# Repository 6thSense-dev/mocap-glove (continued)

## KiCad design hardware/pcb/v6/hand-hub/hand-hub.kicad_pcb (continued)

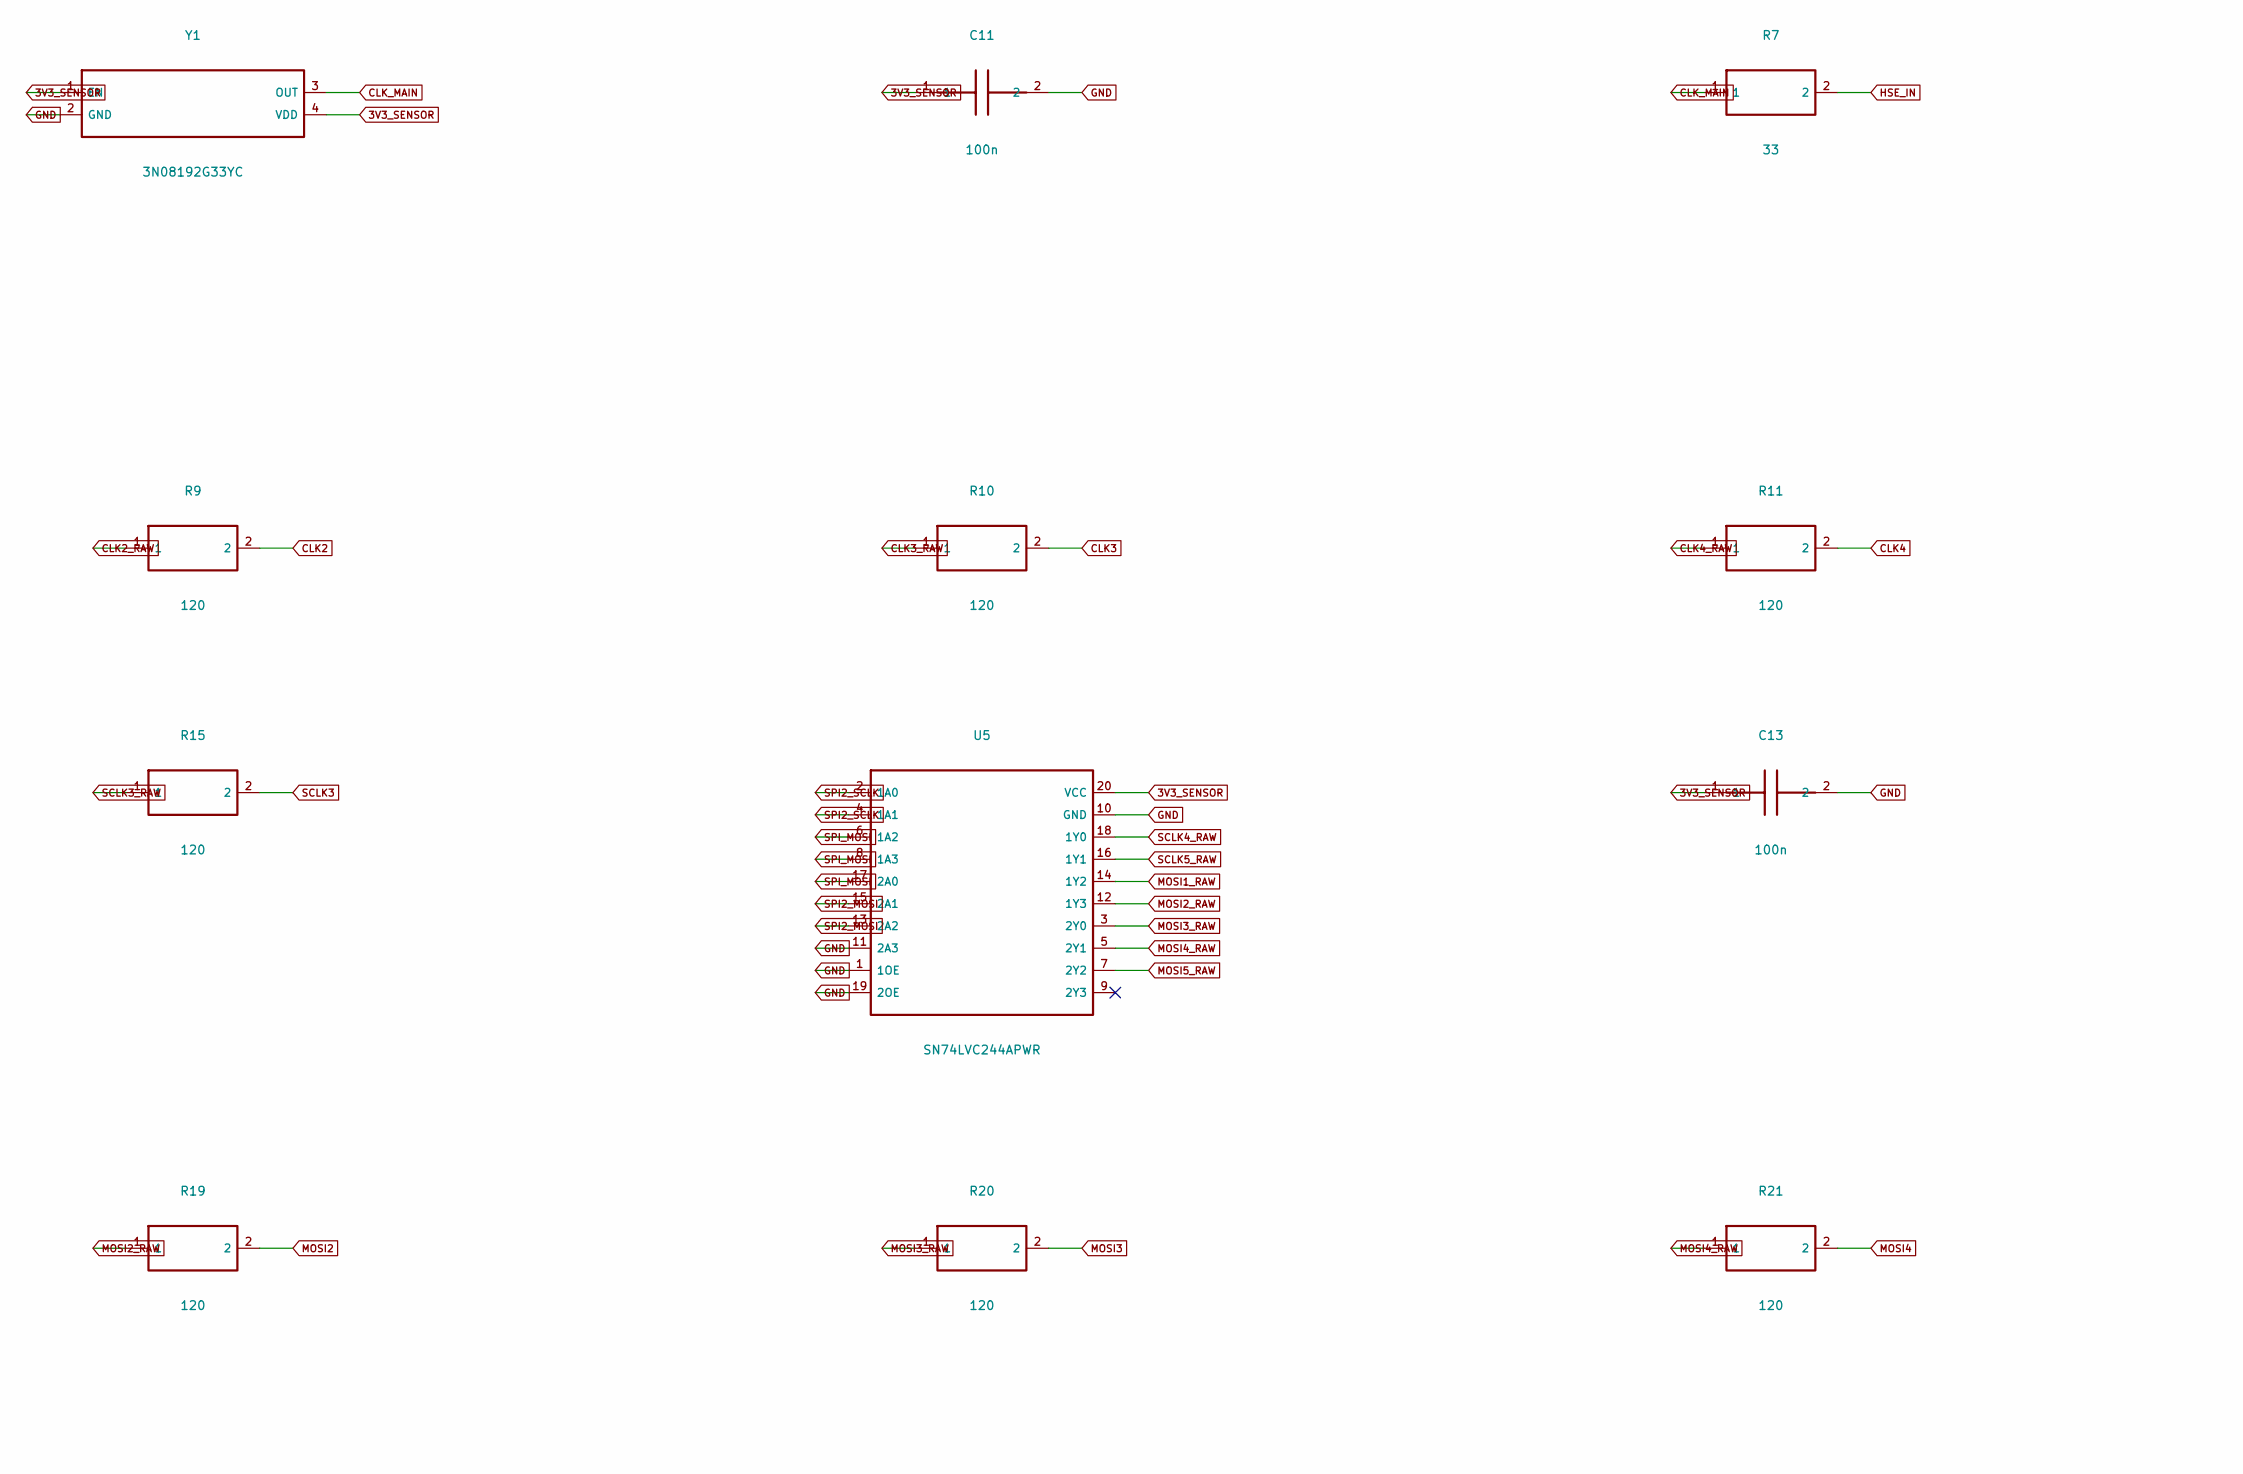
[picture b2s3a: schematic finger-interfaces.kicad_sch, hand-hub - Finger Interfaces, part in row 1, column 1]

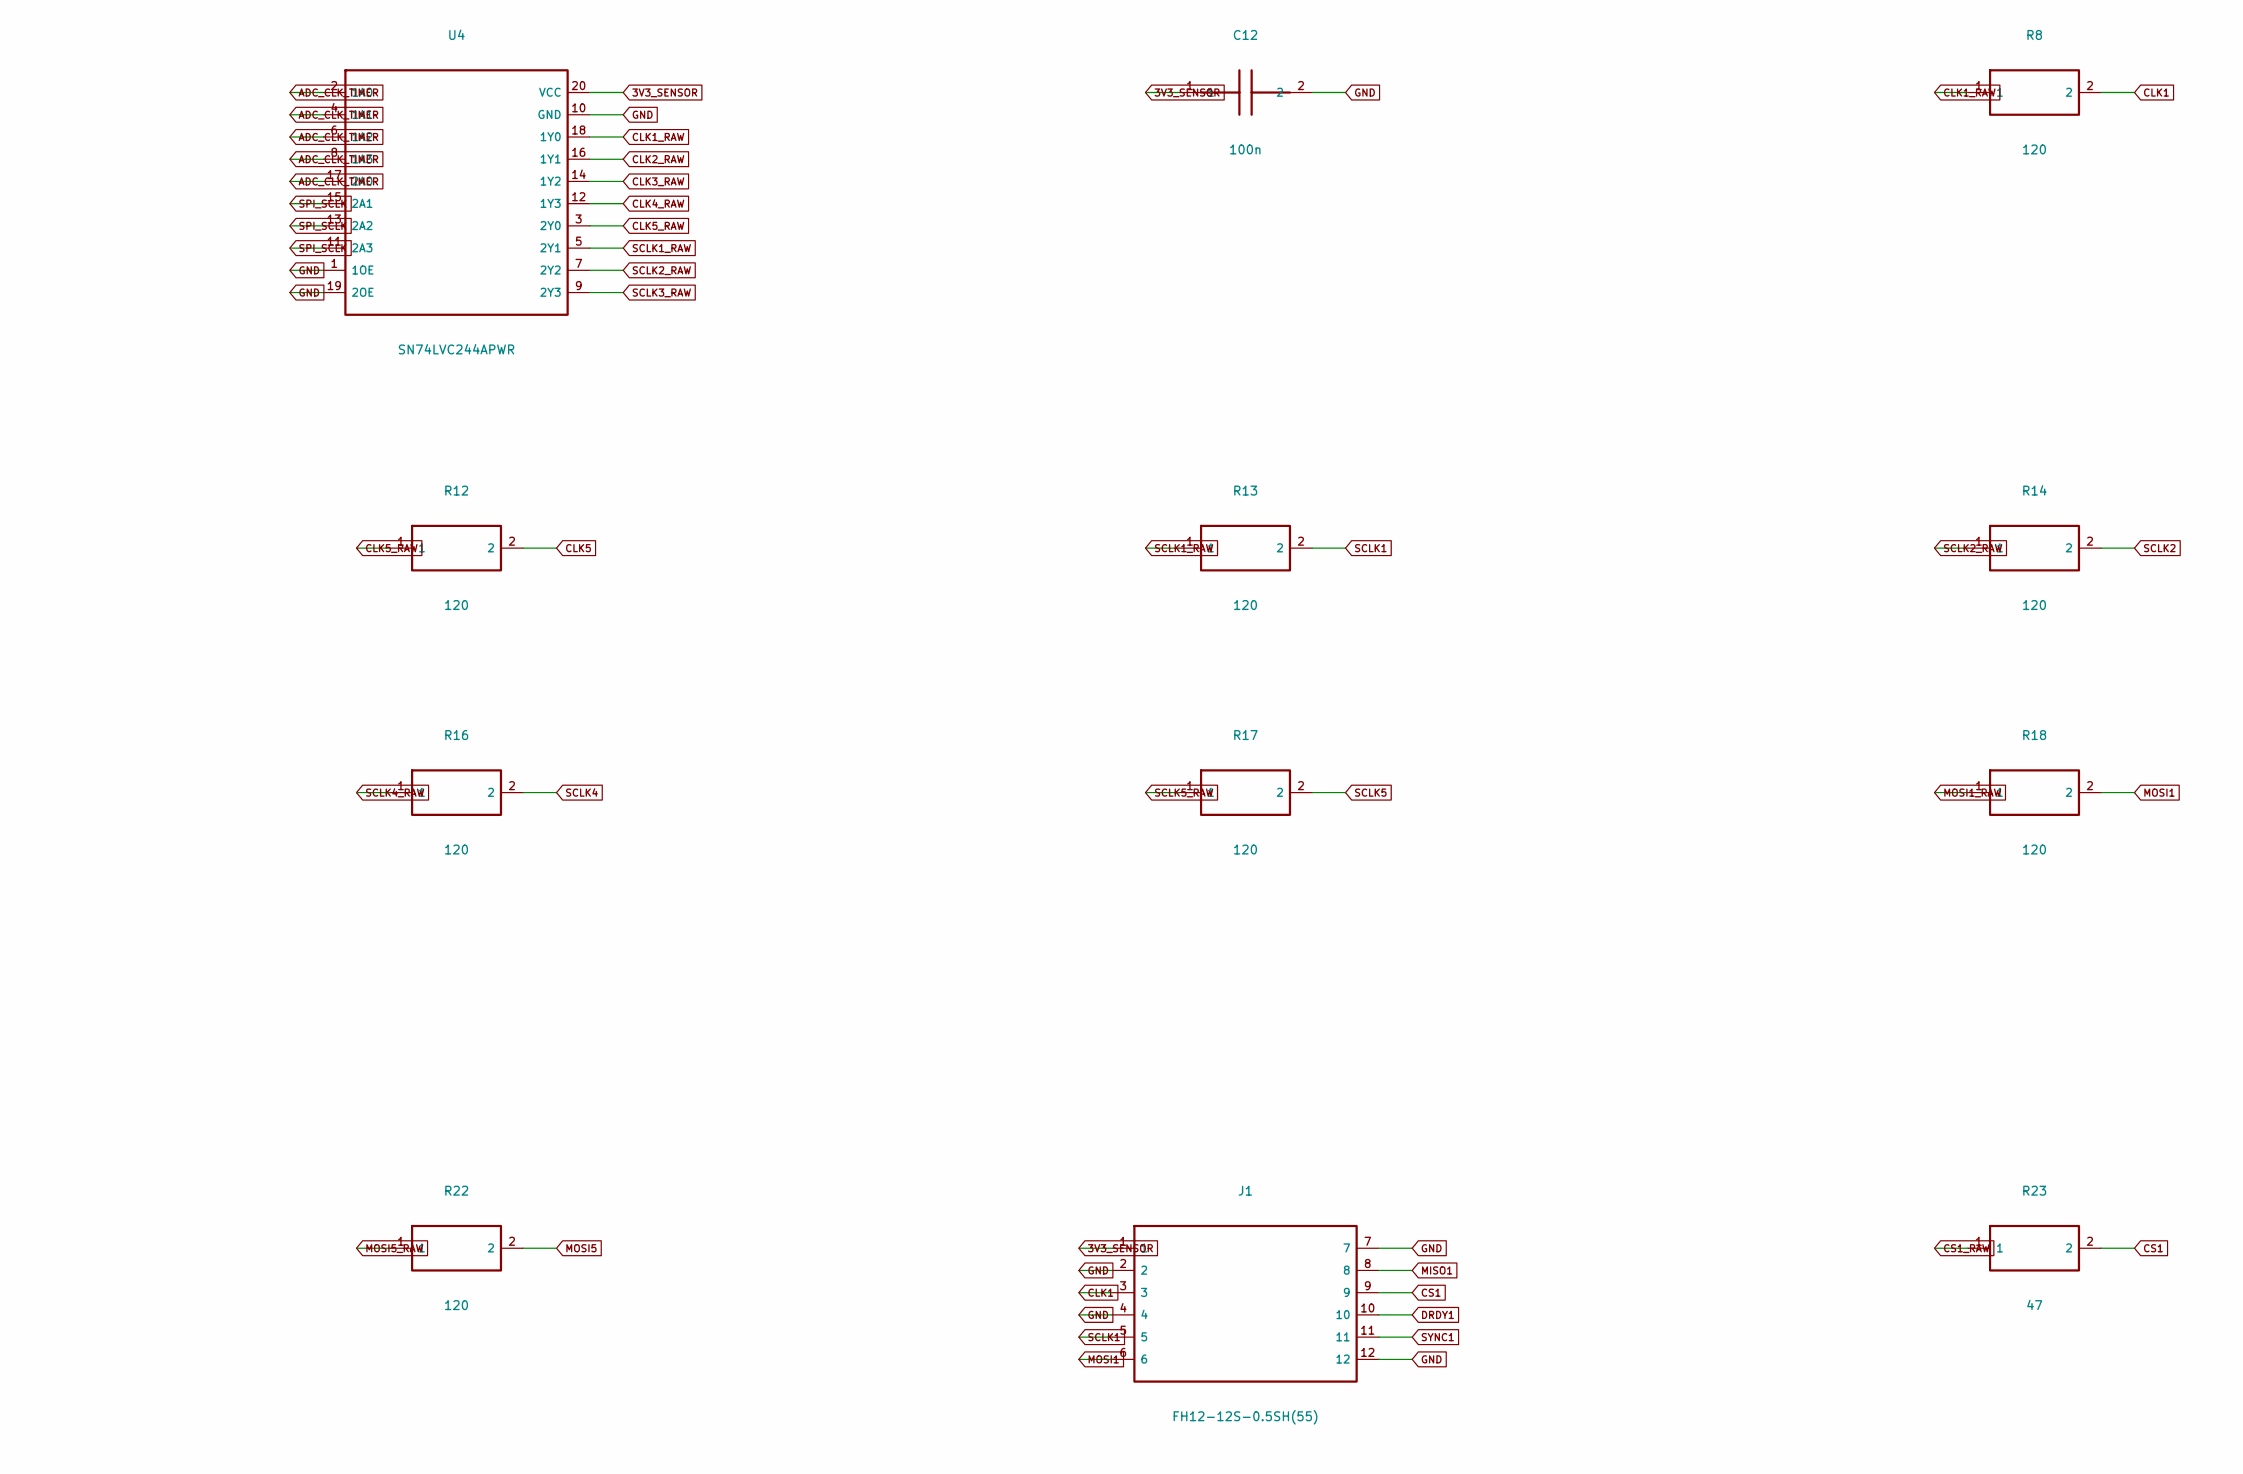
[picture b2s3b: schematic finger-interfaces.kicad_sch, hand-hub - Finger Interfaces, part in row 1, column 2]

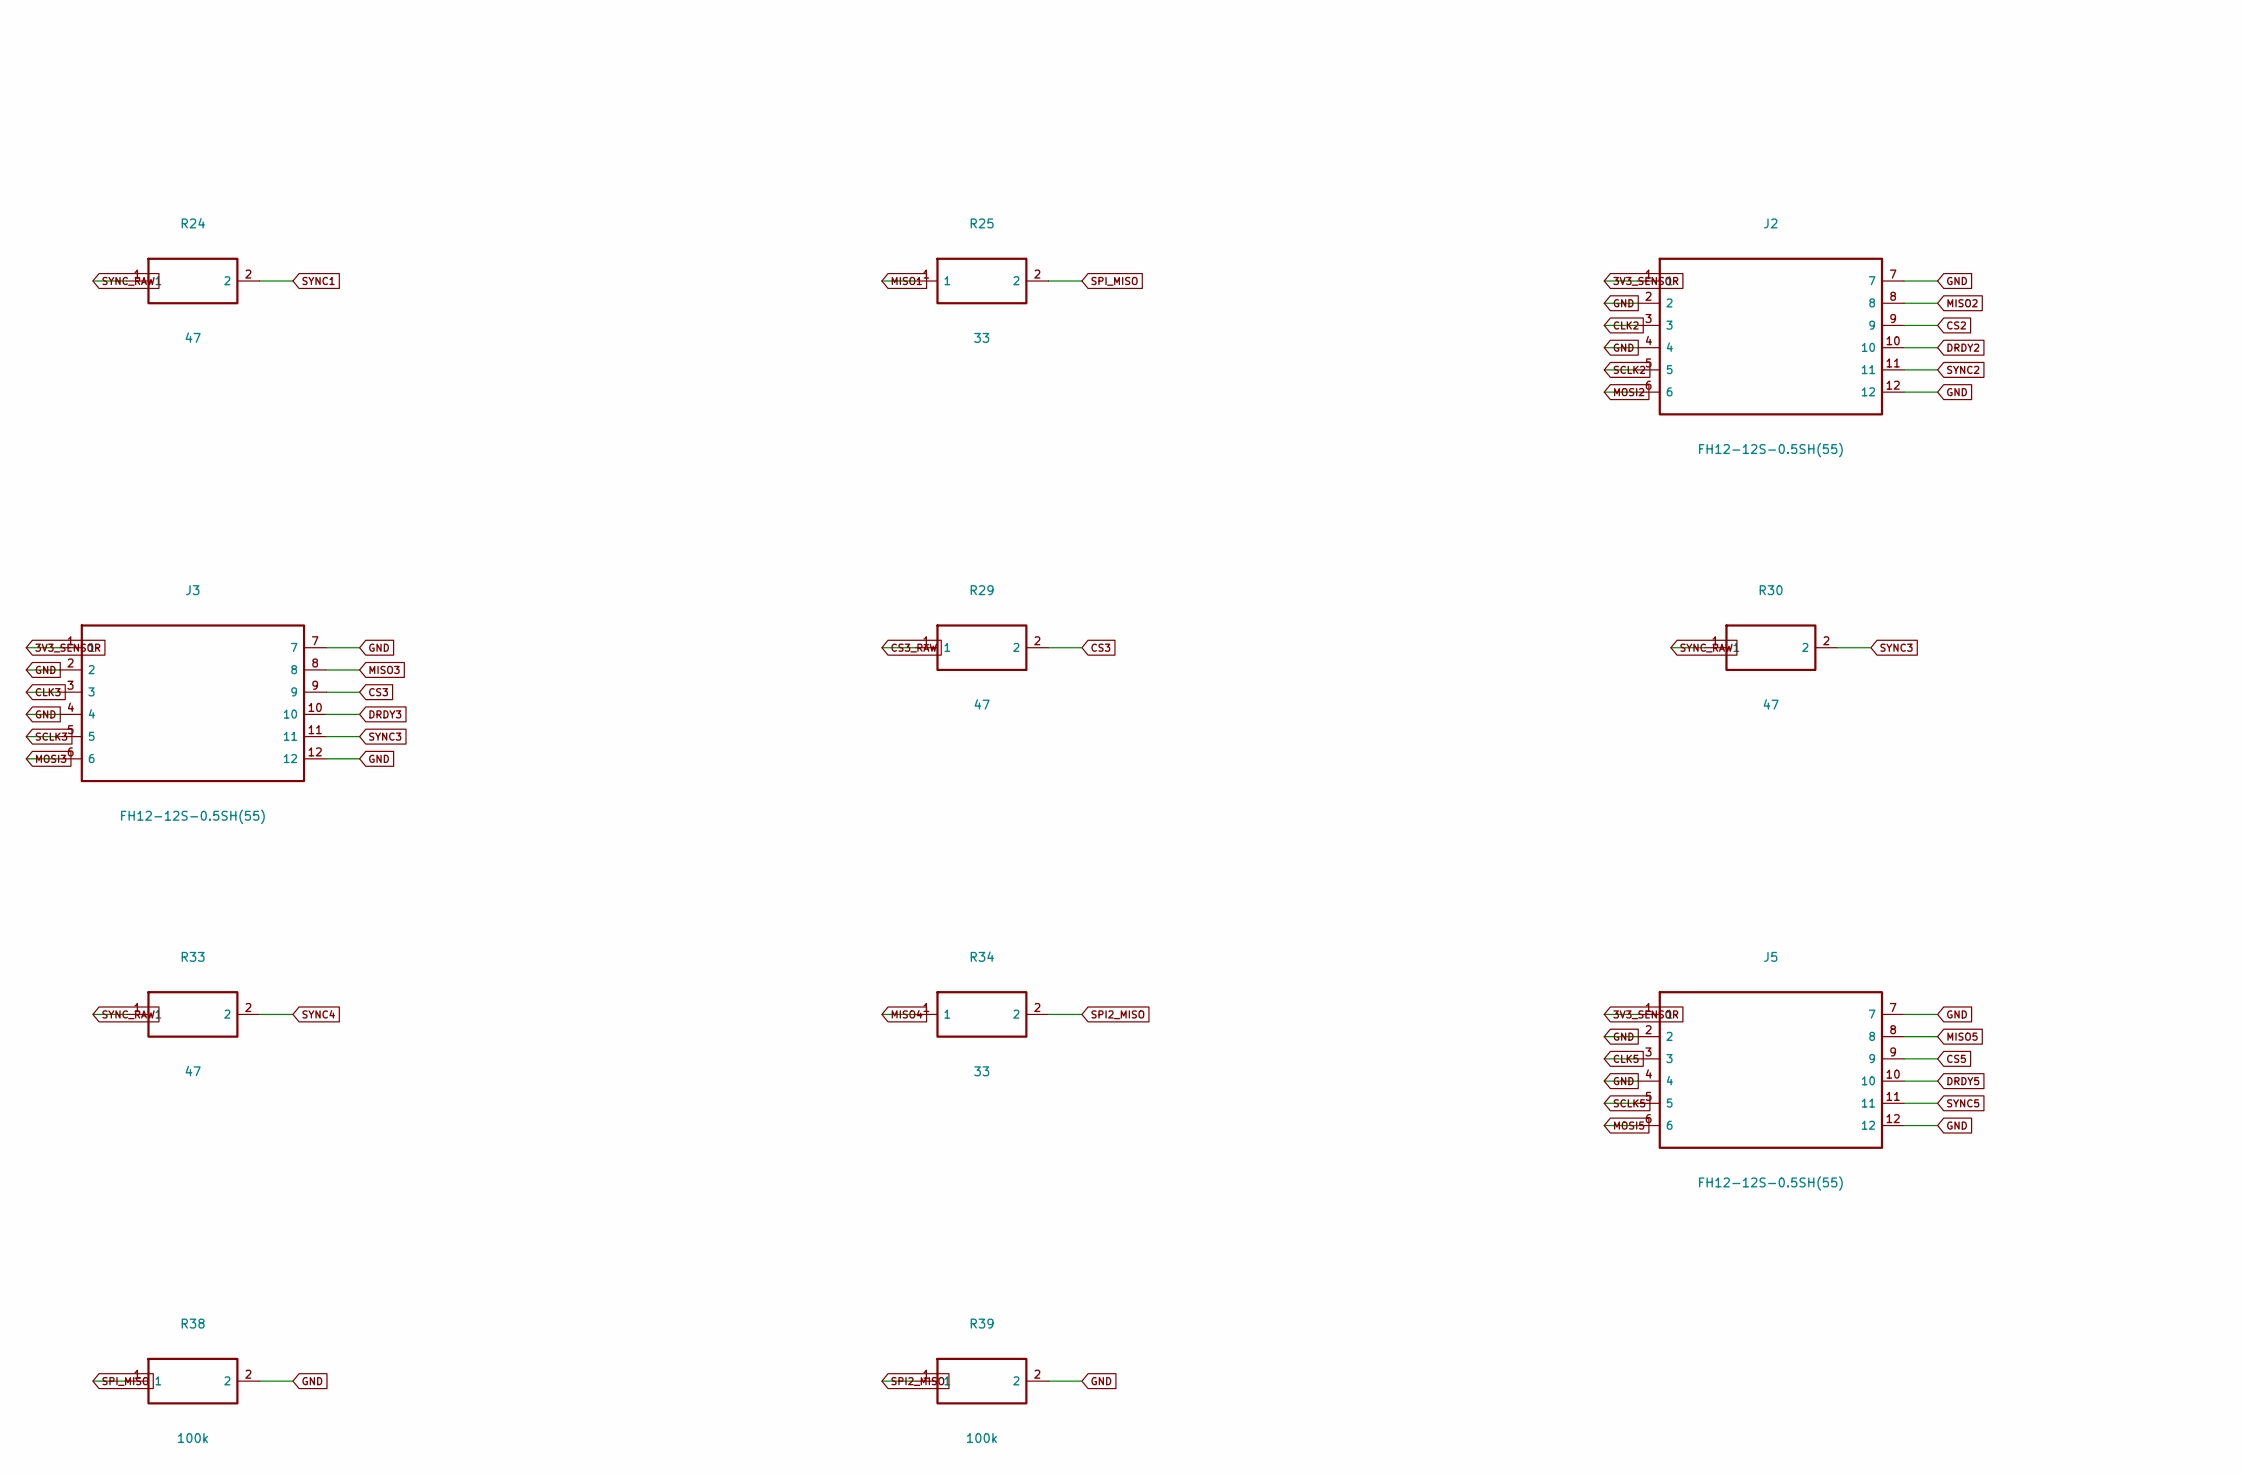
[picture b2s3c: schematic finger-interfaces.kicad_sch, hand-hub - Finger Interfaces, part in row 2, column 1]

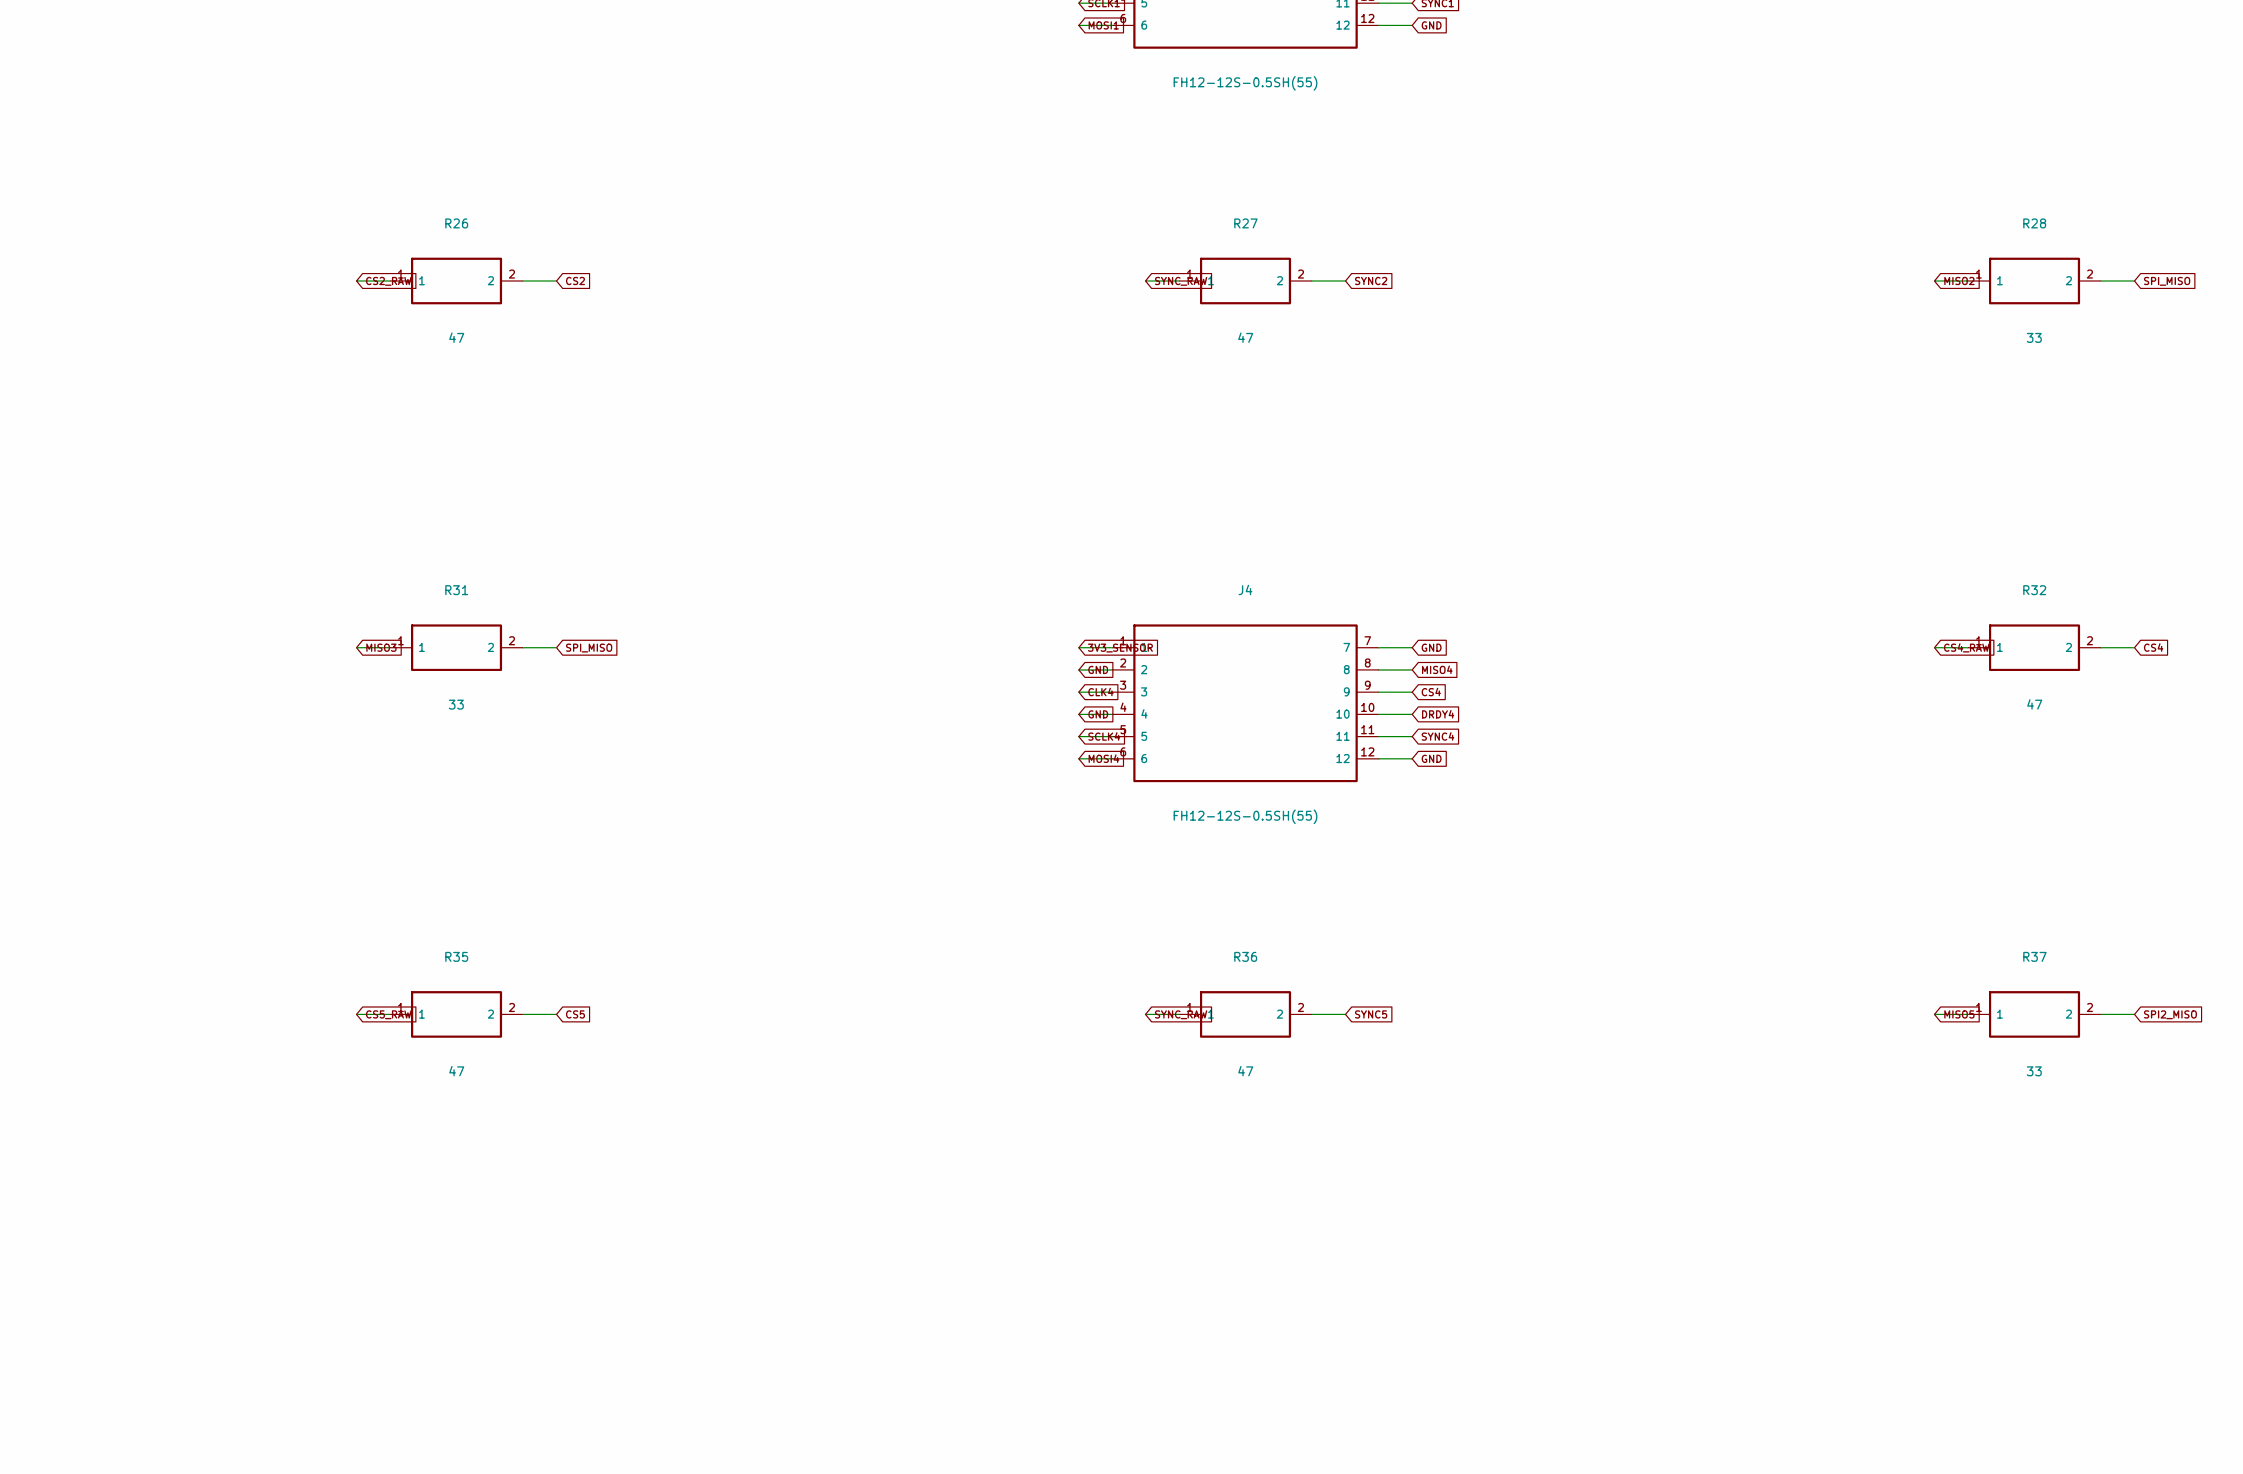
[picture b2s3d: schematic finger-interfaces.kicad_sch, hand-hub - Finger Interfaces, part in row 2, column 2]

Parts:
C11, C12, C13: 100n; C_0402_1005Metric; MPN 100n
J1, J2, J3, J4, J5: FH12-12S-0.5SH(55); Hirose_FH12-12S-0.5SH_1x12-1MP_P0.50mm_Horizontal; MPN FH12-12S-0.5SH(55)
R7, R25, R28, R31, R34, R37: 33; R_0402_1005Metric; MPN 33
R8, R9, R10, R11, R12, R13, R14, R15, R16, R17, R18, R19, R20, R21, R22: 120; R_0402_1005Metric; MPN RC0402FR-07120RL
R23, R24, R26, R27, R29, R30, R32, R33, R35, R36: 47; R_0402_1005Metric; MPN 47
R38, R39: 100k; R_0402_1005Metric; MPN 100k
U4, U5: SN74LVC244APWR; TSSOP-20_4.4x6.5mm_P0.65mm; MPN SN74LVC244APWR
Y1: 3N08192G33YC; SJK_3N_3225; MPN 3N08192G33YC

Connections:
3V3_SENSOR: C11.1, C12.1, C13.1, J1.1, J2.1, J3.1, J4.1, J5.1, U4.20 (VCC), U5.20 (VCC), Y1.1 (EN), Y1.4 (VDD); also elsewhere on the board
ADC_CLK_TIMER: U4.2 (1A0), U4.4 (1A1), U4.6 (1A2), U4.8 (1A3), U4.17 (2A0); also elsewhere on the board
CLK1: J1.3, R8.2
CLK1_RAW: R8.1, U4.18 (1Y0)
CLK2: J2.3, R9.2
CLK2_RAW: R9.1, U4.16 (1Y1)
CLK3: J3.3, R10.2
CLK3_RAW: R10.1, U4.14 (1Y2)
CLK4: J4.3, R11.2
CLK4_RAW: R11.1, U4.12 (1Y3)
CLK5: J5.3, R12.2
CLK5_RAW: R12.1, U4.3 (2Y0)
CLK_MAIN: R7.1, Y1.3 (OUT)
CS1: J1.9, R23.2
CS1_RAW: R23.1; also elsewhere on the board
CS2: J2.9, R26.2
CS2_RAW: R26.1; also elsewhere on the board
CS3: J3.9, R29.2
CS3_RAW: R29.1; also elsewhere on the board
CS4: J4.9, R32.2
CS4_RAW: R32.1; also elsewhere on the board
CS5: J5.9, R35.2
CS5_RAW: R35.1; also elsewhere on the board
DRDY1: J1.10; also elsewhere on the board
DRDY2: J2.10; also elsewhere on the board
DRDY3: J3.10; also elsewhere on the board
DRDY4: J4.10; also elsewhere on the board
DRDY5: J5.10; also elsewhere on the board
GND: C11.2, C12.2, C13.2, J1.2, J1.4, J1.7, J1.12, J2.2, J2.4, J2.7, J2.12, J3.2, J3.4, J3.7, J3.12, J4.2, J4.4, J4.7, J4.12, J5.2, J5.4, J5.7, J5.12, R38.2, R39.2, U4.1 (1OE), U4.10 (GND), U4.19 (2OE), U5.1 (1OE), U5.10 (GND), U5.11 (2A3), U5.19 (2OE), Y1.2 (GND); also elsewhere on the board
HSE_IN: R7.2; also elsewhere on the board
MISO1: J1.8, R25.1
MISO2: J2.8, R28.1
MISO3: J3.8, R31.1
MISO4: J4.8, R34.1
MISO5: J5.8, R37.1
MOSI1: J1.6, R18.2
MOSI1_RAW: R18.1, U5.14 (1Y2)
MOSI2: J2.6, R19.2
MOSI2_RAW: R19.1, U5.12 (1Y3)
MOSI3: J3.6, R20.2
MOSI3_RAW: R20.1, U5.3 (2Y0)
MOSI4: J4.6, R21.2
MOSI4_RAW: R21.1, U5.5 (2Y1)
MOSI5: J5.6, R22.2
MOSI5_RAW: R22.1, U5.7 (2Y2)
SCLK1: J1.5, R13.2
SCLK1_RAW: R13.1, U4.5 (2Y1)
SCLK2: J2.5, R14.2
SCLK2_RAW: R14.1, U4.7 (2Y2)
SCLK3: J3.5, R15.2
SCLK3_RAW: R15.1, U4.9 (2Y3)
SCLK4: J4.5, R16.2
SCLK4_RAW: R16.1, U5.18 (1Y0)
SCLK5: J5.5, R17.2
SCLK5_RAW: R17.1, U5.16 (1Y1)
SPI2_MISO: R34.2, R37.2, R39.1; also elsewhere on the board
SPI2_MOSI: U5.13 (2A2), U5.15 (2A1); also elsewhere on the board
SPI2_SCLK: U5.2 (1A0), U5.4 (1A1); also elsewhere on the board
SPI_MISO: R25.2, R28.2, R31.2, R38.1; also elsewhere on the board
SPI_MOSI: U5.6 (1A2), U5.8 (1A3), U5.17 (2A0); also elsewhere on the board
SPI_SCLK: U4.11 (2A3), U4.13 (2A2), U4.15 (2A1); also elsewhere on the board
SYNC1: J1.11, R24.2
SYNC2: J2.11, R27.2
SYNC3: J3.11, R30.2
SYNC4: J4.11, R33.2
SYNC5: J5.11, R36.2
SYNC_RAW: R24.1, R27.1, R30.1, R33.1, R36.1; also elsewhere on the board

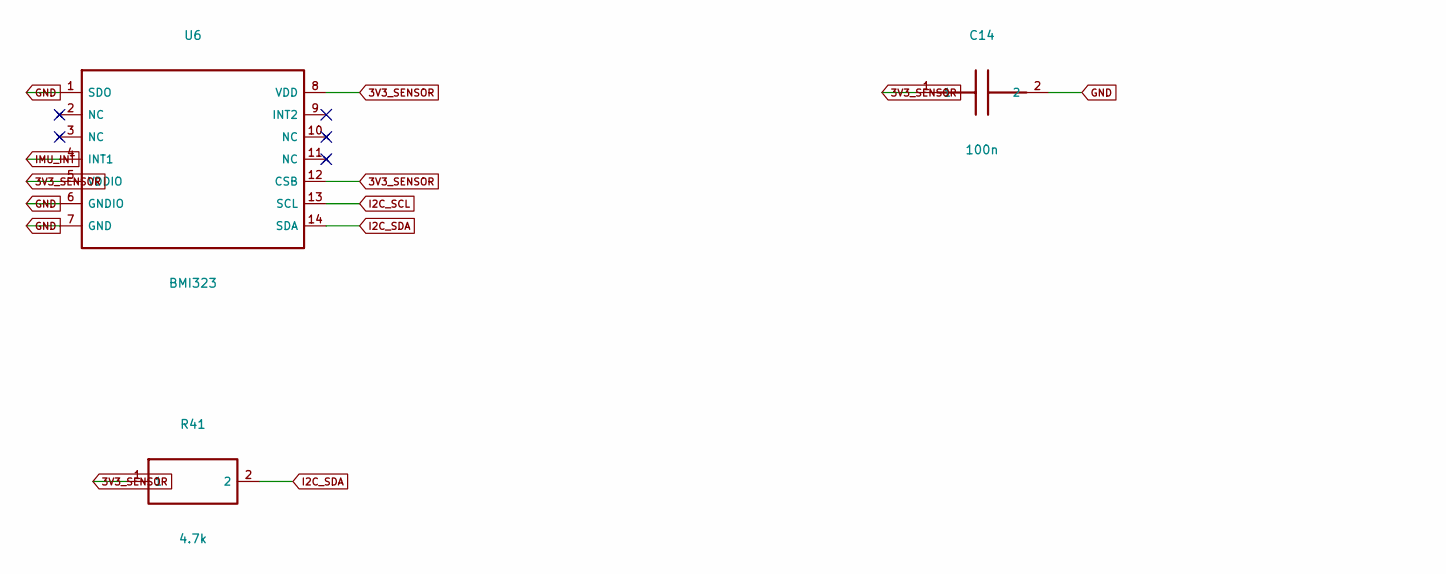
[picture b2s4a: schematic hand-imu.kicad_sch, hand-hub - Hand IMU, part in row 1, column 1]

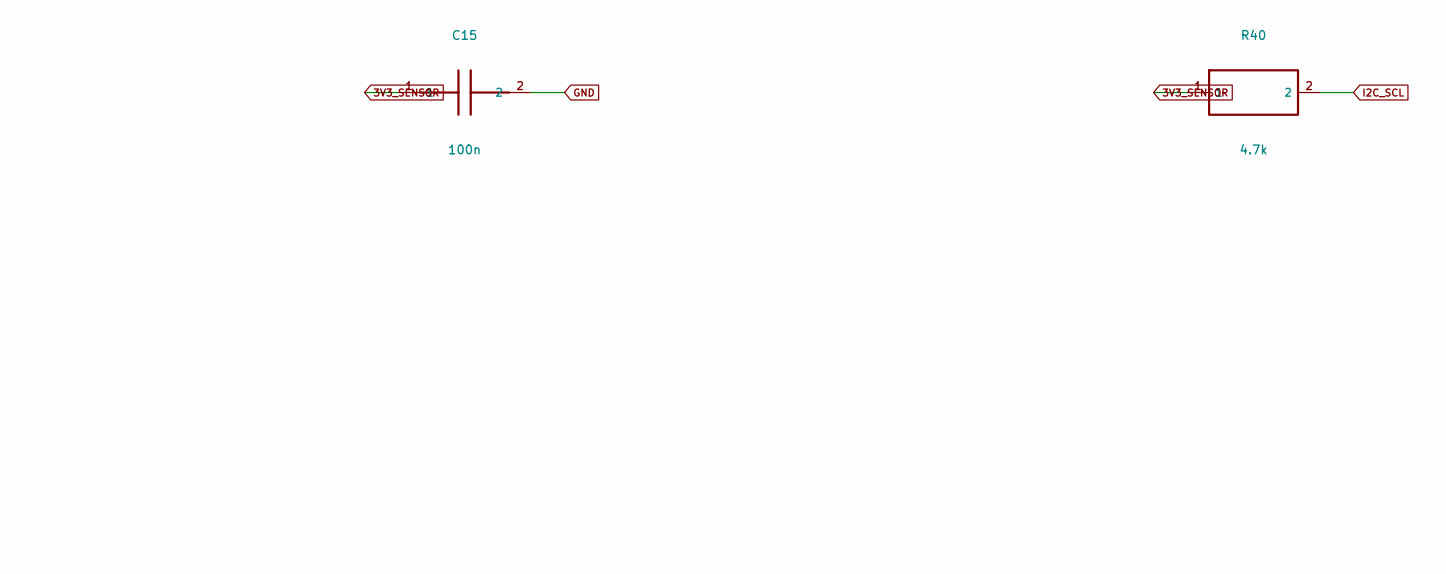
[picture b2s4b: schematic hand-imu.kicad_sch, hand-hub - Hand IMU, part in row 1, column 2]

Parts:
C14, C15: 100n; C_0402_1005Metric; MPN 100n
R40, R41: 4.7k; R_0402_1005Metric; MPN 4.7k
U6: BMI323; Bosch_LGA-14_3x2.5mm_P0.5mm; MPN BMI323

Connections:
3V3_SENSOR: C14.1, C15.1, R40.1, R41.1, U6.5 (VDDIO), U6.8 (VDD), U6.12 (CSB); also elsewhere on the board
GND: C14.2, C15.2, U6.1 (SDO), U6.6 (GNDIO), U6.7 (GND); also elsewhere on the board
I2C_SCL: R40.2, U6.13 (SCL); also elsewhere on the board
I2C_SDA: R41.2, U6.14 (SDA); also elsewhere on the board
IMU_INT: U6.4 (INT1); also elsewhere on the board
